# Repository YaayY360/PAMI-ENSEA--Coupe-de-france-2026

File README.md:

# 🔧 Coupe de france de robotique 2026 - PAMI ENSEA 

> **Objectif :** Conception et fabrication d'un robot PAMI (Petit Actionneur Motorisé Indépendant) respectant les modalités attendues pour la coupe de france de robotique 2026.
> 
> **Membres de l'équipe :**
> 
> CHERFI Iftene (1G1)
> 
> EL BAROUD Elias (1G1)
> 
> GRAVE Yanis (1G1)
> 
> LINOT Jean-Bosco (1G1)
> 
> MALEPART Alexandre (1G3)
>
> NEJJARI Mouaad (1G3)
>
> SURESHKUMAR Valentin (1G1)
---

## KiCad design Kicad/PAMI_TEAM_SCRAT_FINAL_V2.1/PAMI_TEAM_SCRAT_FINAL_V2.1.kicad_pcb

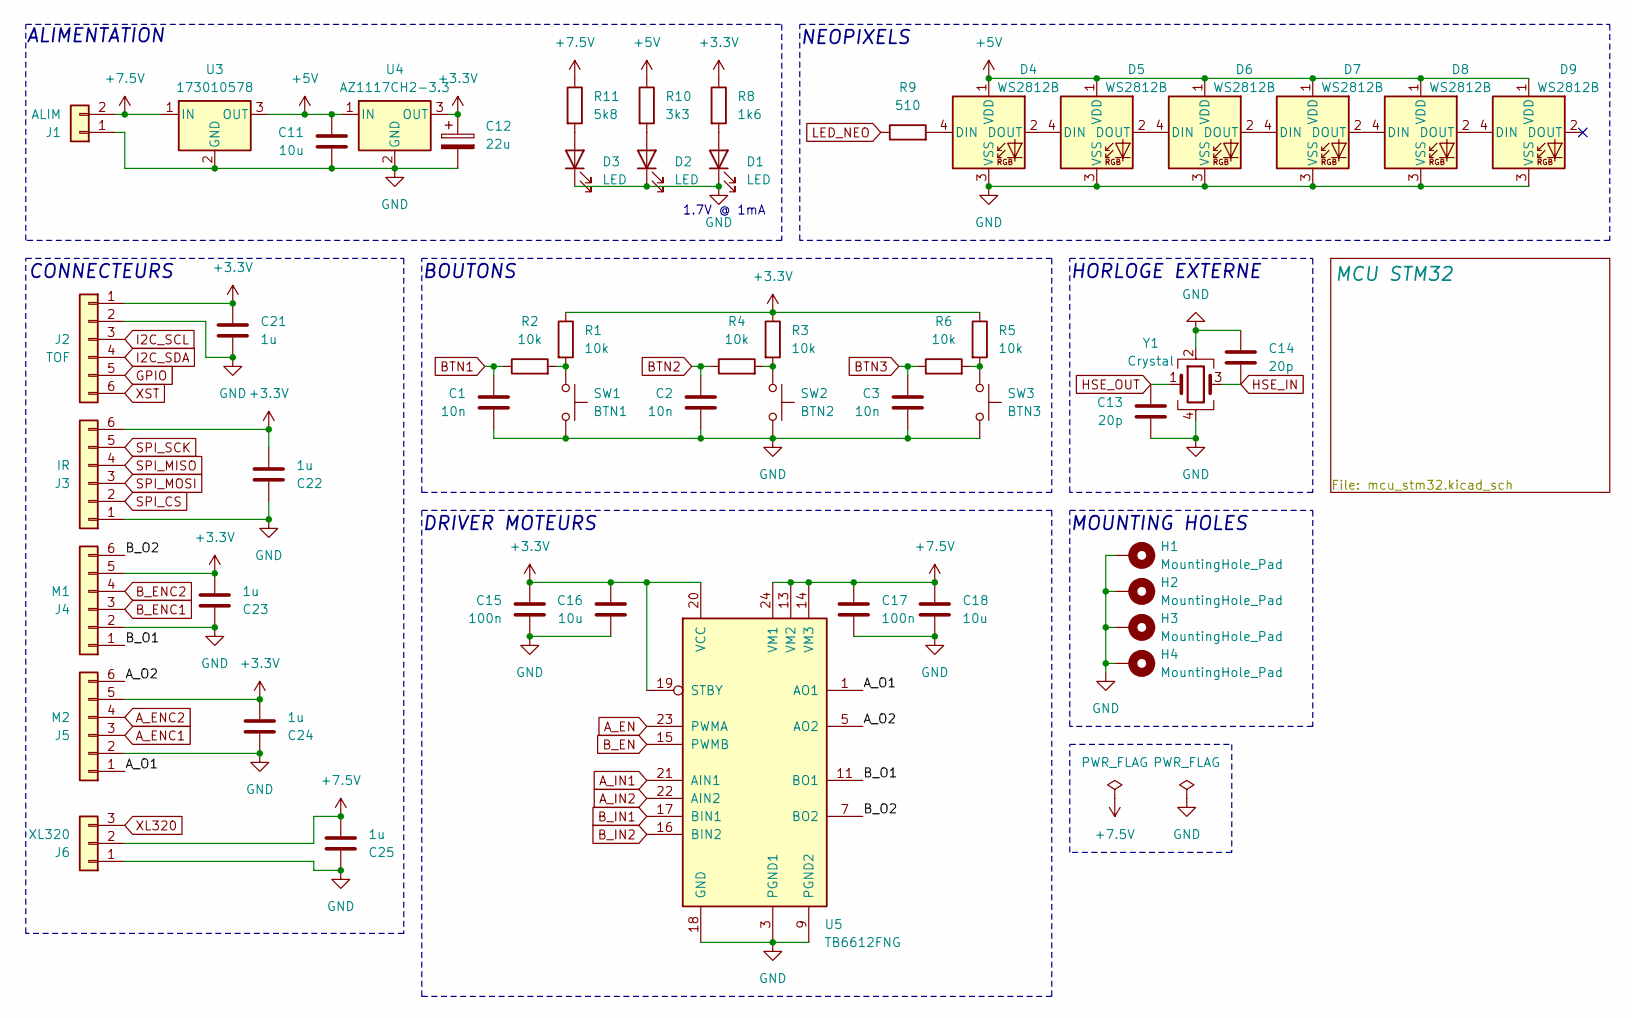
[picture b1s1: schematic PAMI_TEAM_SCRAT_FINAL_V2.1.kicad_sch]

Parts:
C1, C2, C3: 10n; C_0603_1608Metric
C11, C16, C18: 10u; C_0603_1608Metric
C12: 22u; CP_Elec_5x5.4
C13, C14: 20p; C_0603_1608Metric
C15, C17: 100n; C_0603_1608Metric
C21, C22, C23, C24, C25: 1u; C_0603_1608Metric
D1, D2, D3: LED; LED_0603_1608Metric; MPN 150060RS55040
D4, D5, D6, D7, D8, D9: WS2812B; LED_WS2812B_PLCC4_5.0x5.0mm_P3.2mm
H1, H2, H3, H4: MountingHole_Pad; MountingHole_3.2mm_M3_DIN965_Pad
J1: ALIM; JST_XH_B2B-XH-A_1x02_P2.50mm_Vertical
J2: TOF; PinSocket_1x06_P2.54mm_Horizontal
J3: IR; JST_XH_B6B-XH-A_1x06_P2.50mm_Vertical
J4: M1; JST_XH_B6B-XH-A_1x06_P2.50mm_Vertical
J5: M2; JST_XH_B6B-XH-A_1x06_P2.50mm_Vertical
J6: XL320; JST_XH_B3B-XH-A_1x03_P2.50mm_Vertical
R1, R2, R3, R4, R5, R6: 10k; R_0603_1608Metric
R8: 1k6; R_0603_1608Metric
R9: 510; R_0603_1608Metric
R10: 3k3; R_0603_1608Metric
R11: 5k8; R_0603_1608Metric
SW1: BTN1; SW_SPST_PTS645Sx43SMTR92
SW2: BTN2; SW_SPST_PTS645Sx43SMTR92
SW3: BTN3; SW_SPST_PTS645Sx43SMTR92
U3: 173010578; Converter_DCDC_RECOM_R-78E-0.5_THT; MPN 173010578
U4: AZ1117CH2-3.3; SOT-223-3_TabPin2
U5: TB6612FNG; SSOP-24_5.3x8.2mm_P0.65mm
Y1: Crystal; Crystal_SMD_7050-4Pin_7.0x5.0mm

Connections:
+3.3V: C12.1, C15.1, C16.1, C21.1, C22.2, C23.2, C24.2, J2.1, J3.6, J4.5, J5.5, R1.1, R3.1, R5.1, R8.1, U4.3 (OUT), U5.19 (STBY), U5.20 (VCC); also elsewhere on the board
+5V: C11.1, D4.1 (VDD), D5.1 (VDD), D6.1 (VDD), D7.1 (VDD), D8.1 (VDD), D9.1 (VDD), R10.1, U3.3 (OUT), U4.1 (IN)
+7.5V: C17.1, C18.1, C25.2, J1.2, J6.2, R11.1, U3.1 (IN), U5.13 (VM2), U5.14 (VM3), U5.24 (VM1)
/A_O1: J5.1, U5.1 (AO1), U5.2 (AO1)
/A_O2: J5.6, U5.5 (AO2), U5.6 (AO2)
/B_O1: J4.1, U5.11 (BO1), U5.12 (BO1)
/B_O2: J4.6, U5.7 (BO2), U5.8 (BO2)
A_EN: U5.23 (PWMA); also elsewhere on the board
A_ENC1: J5.3; also elsewhere on the board
A_ENC2: J5.4; also elsewhere on the board
A_IN1: U5.21 (AIN1); also elsewhere on the board
A_IN2: U5.22 (AIN2); also elsewhere on the board
BTN1: C1.1, R2.1; also elsewhere on the board
BTN2: C2.1, R4.1; also elsewhere on the board
BTN3: C3.1, R6.1; also elsewhere on the board
B_EN: U5.15 (PWMB); also elsewhere on the board
B_ENC1: J4.3; also elsewhere on the board
B_ENC2: J4.4; also elsewhere on the board
B_IN1: U5.17 (BIN1); also elsewhere on the board
B_IN2: U5.16 (BIN2); also elsewhere on the board
GND: C1.2, C2.2, C3.2, C11.2, C12.2, C13.2, C14.1, C15.2, C16.2, C17.2, C18.2, C21.2, C22.1, C23.1, C24.1, C25.1, D1.1 (K), D2.1 (K), D3.1 (K), D4.3 (VSS), D5.3 (VSS), D6.3 (VSS), D7.3 (VSS), D8.3 (VSS), D9.3 (VSS), H1.1, H2.1, H3.1, H4.1, J1.1, J2.2, J3.1, J4.2, J5.2, J6.1, SW1.2, SW2.2, SW3.2, U3.2 (GND), U4.2 (GND), U5.3 (PGND1), U5.4 (PGND1), U5.9 (PGND2), U5.10 (PGND2), U5.18 (GND), Y1.2, Y1.4; also elsewhere on the board
GPIO: J2.5; also elsewhere on the board
HSE_IN: C14.2, Y1.3; also elsewhere on the board
HSE_OUT: C13.1, Y1.1; also elsewhere on the board
I2C_SCL: J2.3; also elsewhere on the board
I2C_SDA: J2.4; also elsewhere on the board
LED_NEO: R9.1; also elsewhere on the board
unnamed: D1.2 (A), R8.2
unnamed: D2.2 (A), R10.2
unnamed: D3.2 (A), R11.2
unnamed: D4.4 (DIN), R9.2
unnamed: D4.2 (DOUT), D5.4 (DIN)
unnamed: D5.2 (DOUT), D6.4 (DIN)
unnamed: D6.2 (DOUT), D7.4 (DIN)
unnamed: D7.2 (DOUT), D8.4 (DIN)
unnamed: D8.2 (DOUT), D9.4 (DIN)
unnamed: R1.2, R2.2, SW1.1
unnamed: R3.2, R4.2, SW2.1
unnamed: R5.2, R6.2, SW3.1
SPI_CS: J3.2; also elsewhere on the board
SPI_MISO: J3.4; also elsewhere on the board
SPI_MOSI: J3.3; also elsewhere on the board
SPI_SCK: J3.5; also elsewhere on the board
XL320: J6.3; also elsewhere on the board
XST: J2.6; also elsewhere on the board

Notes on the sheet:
CONNECTEURS
MOUNTING HOLES
BOUTONS
NEOPIXELS
HORLOGE EXTERNE
DRIVER MOTEURS
ALIMENTATION
1.7V @ 1mA

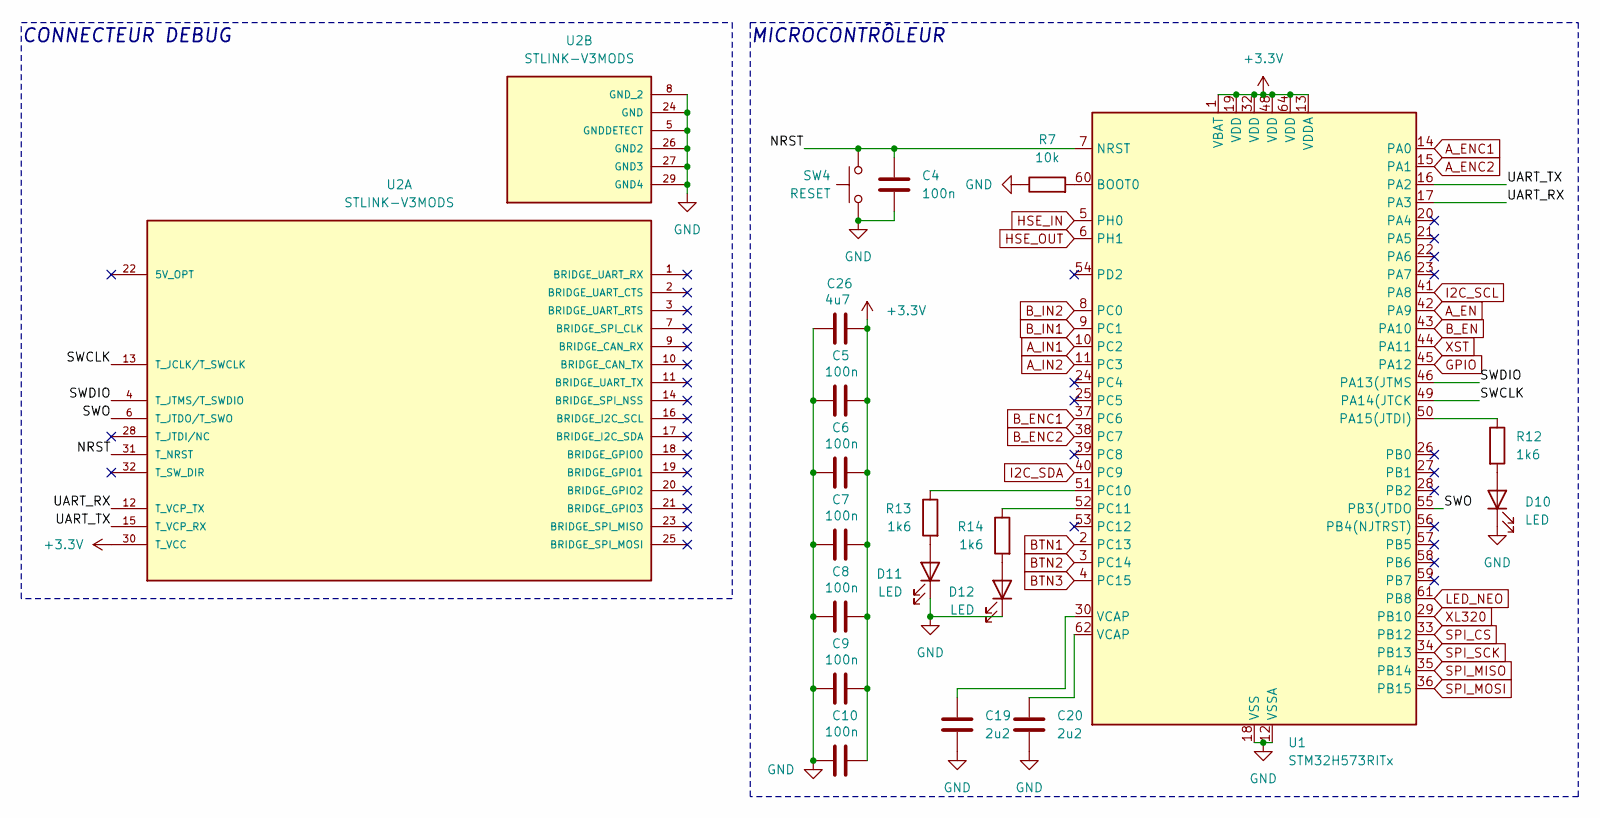
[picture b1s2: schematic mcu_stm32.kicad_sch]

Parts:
C4, C5, C6, C7, C8, C9, C10: 100n; C_0603_1608Metric
C19, C20: 2u2; C_0603_1608Metric
C26: 4u7; C_0603_1608Metric
D10, D11, D12: LED; LED_0603_1608Metric; MPN 150060RS55040
R7: 10k; R_0603_1608Metric
R12, R13, R14: 1k6; R_0603_1608Metric
SW4: RESET; SW_SPST_PTS645Sx43SMTR92
U1: STM32H573RITx; LQFP-64_10x10mm_P0.5mm
U2: STLINK-V3MODS; MODULE_STLINK-V3MODS; PARTREV 1

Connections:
+3.3V: C5.2, C6.2, C7.2, C8.2, C9.2, C10.2, C26.2, U1.1 (VBAT), U1.13 (VDDA), U1.19 (VDD), U1.32 (VDD), U1.48 (VDD), U1.64 (VDD), U2.30 (T_VCC); also elsewhere on the board
/MCU STM32/NRST: C4.1, SW4.1, U1.7 (NRST), U2.31 (T_NRST)
/MCU STM32/SWCLK: U1.49 (PA14(JTCK), U2.13 (T_JCLK/T_SWCLK)
/MCU STM32/SWDIO: U1.46 (PA13(JTMS), U2.4 (T_JTMS/T_SWDIO)
/MCU STM32/SWO: U1.55 (PB3(JTDO), U2.6 (T_JTDO/T_SWO)
/MCU STM32/UART_RX: U1.17 (PA3), U2.12 (T_VCP_TX)
/MCU STM32/UART_TX: U1.16 (PA2), U2.15 (T_VCP_RX)
A_EN: U1.42 (PA9); also elsewhere on the board
A_ENC1: U1.14 (PA0); also elsewhere on the board
A_ENC2: U1.15 (PA1); also elsewhere on the board
A_IN1: U1.10 (PC2); also elsewhere on the board
A_IN2: U1.11 (PC3); also elsewhere on the board
BTN1: U1.2 (PC13); also elsewhere on the board
BTN2: U1.3 (PC14); also elsewhere on the board
BTN3: U1.4 (PC15); also elsewhere on the board
B_EN: U1.43 (PA10); also elsewhere on the board
B_ENC1: U1.37 (PC6); also elsewhere on the board
B_ENC2: U1.38 (PC7); also elsewhere on the board
B_IN1: U1.9 (PC1); also elsewhere on the board
B_IN2: U1.8 (PC0); also elsewhere on the board
GND: C4.2, C5.1, C6.1, C7.1, C8.1, C9.1, C10.1, C19.2, C20.2, C26.1, D10.1 (K), D11.1 (K), D12.1 (K), R7.1, SW4.2, U1.12 (VSSA), U1.18 (VSS), U1.31 (VSS), U1.47 (VSS), U1.63 (VSS), U2.5 (GNDDETECT), U2.8 (GND_2), U2.24 (GND), U2.26 (GND2), U2.27 (GND3), U2.29 (GND4); also elsewhere on the board
GPIO: U1.45 (PA12); also elsewhere on the board
HSE_IN: U1.5 (PH0); also elsewhere on the board
HSE_OUT: U1.6 (PH1); also elsewhere on the board
I2C_SCL: U1.41 (PA8); also elsewhere on the board
I2C_SDA: U1.40 (PC9); also elsewhere on the board
LED_NEO: U1.61 (PB8); also elsewhere on the board
unnamed: C19.1, U1.30 (VCAP)
unnamed: C20.1, U1.62 (VCAP)
unnamed: D10.2 (A), R12.2
unnamed: D11.2 (A), R13.2
unnamed: D12.2 (A), R14.2
unnamed: R7.2, U1.60 (BOOT0)
unnamed: R12.1, U1.50 (PA15(JTDI))
unnamed: R13.1, U1.51 (PC10)
unnamed: R14.1, U1.52 (PC11)
SPI_CS: U1.33 (PB12); also elsewhere on the board
SPI_MISO: U1.35 (PB14); also elsewhere on the board
SPI_MOSI: U1.36 (PB15); also elsewhere on the board
SPI_SCK: U1.34 (PB13); also elsewhere on the board
XL320: U1.29 (PB10); also elsewhere on the board
XST: U1.44 (PA11); also elsewhere on the board

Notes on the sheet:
CONNECTEUR DEBUG
MICROCONTRÔLEUR

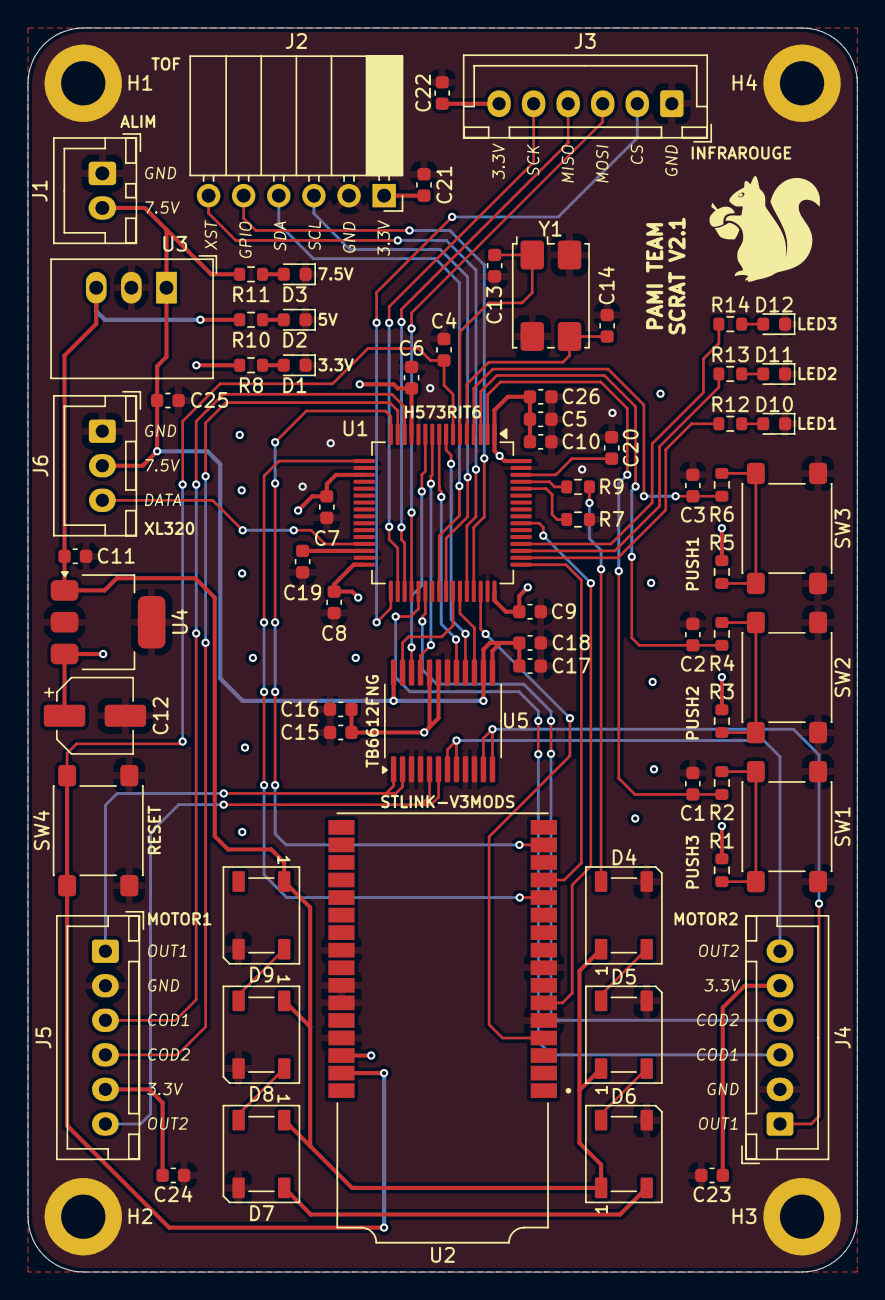
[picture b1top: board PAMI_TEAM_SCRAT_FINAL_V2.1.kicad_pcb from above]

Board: 4 copper layers, 60.0 x 90.0 mm, 72 parts (0 on the bottom side), 60 nets.

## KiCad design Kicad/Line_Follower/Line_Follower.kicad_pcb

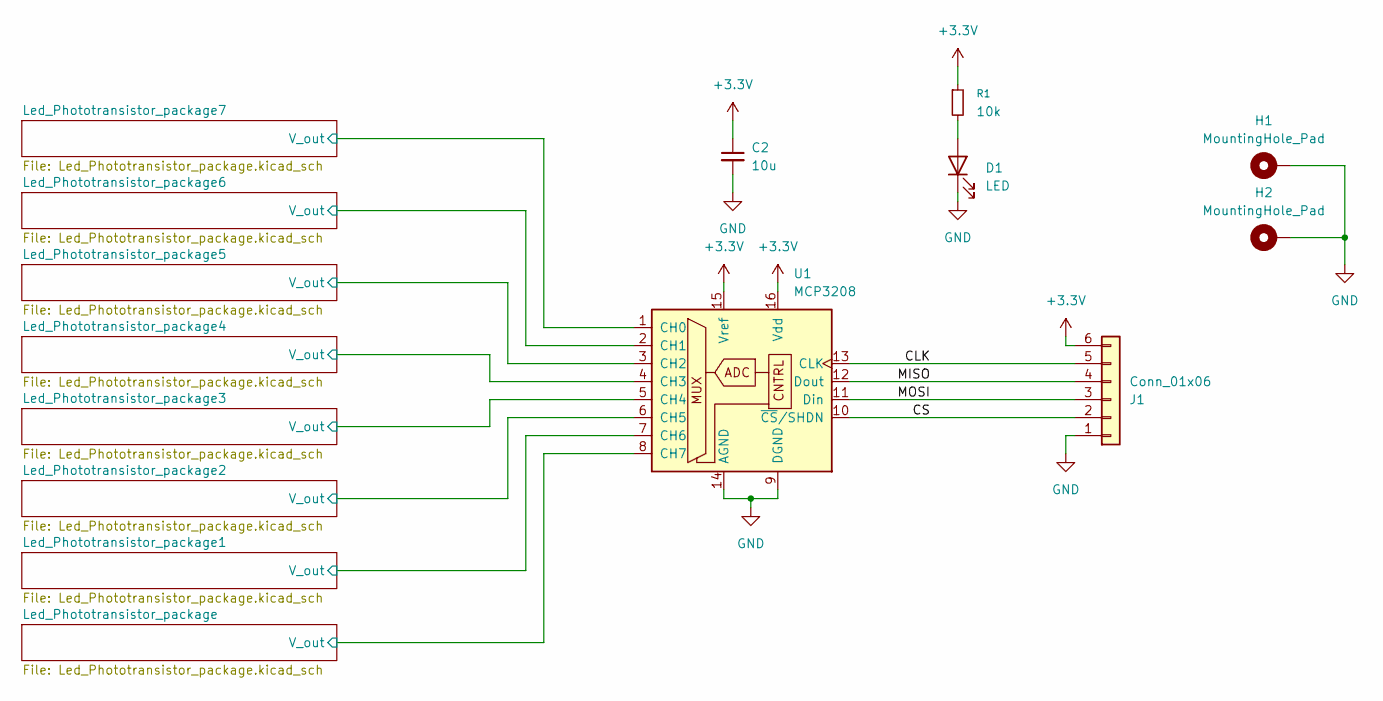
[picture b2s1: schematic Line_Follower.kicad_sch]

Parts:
C2: 10u; C_0603_1608Metric
D1: LED
H1, H2: MountingHole_Pad
J1: Conn_01x06
R1: 10k
U1: MCP3208

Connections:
+3.3V: C2.1, J1.6, R1.1, U1.15 (Vref), U1.16 (Vdd); also elsewhere on the board
/CLK: J1.5, U1.13 (CLK)
/CS: J1.2, U1.10 (~CS/SHDN)
/Led_Phototransistor_package1/V_out: U1.7 (CH6); also elsewhere on the board
/Led_Phototransistor_package2/V_out: U1.6 (CH5); also elsewhere on the board
/Led_Phototransistor_package3/V_out: U1.5 (CH4); also elsewhere on the board
/Led_Phototransistor_package4/V_out: U1.4 (CH3); also elsewhere on the board
/Led_Phototransistor_package5/V_out: U1.3 (CH2); also elsewhere on the board
/Led_Phototransistor_package6/V_out: U1.2 (CH1); also elsewhere on the board
/Led_Phototransistor_package7/V_out: U1.1 (CH0); also elsewhere on the board
/Led_Phototransistor_package/V_out: U1.8 (CH7); also elsewhere on the board
/MISO: J1.4, U1.12 (Dout)
/MOSI: J1.3, U1.11 (Din)
GND: C2.2, D1.1 (K), H1.1, H2.1, J1.1, U1.9 (DGND), U1.14 (AGND); also elsewhere on the board
unnamed: D1.2 (A), R1.2

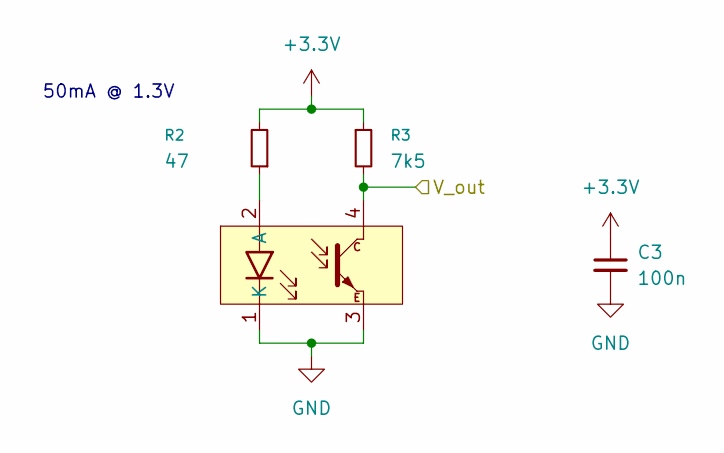
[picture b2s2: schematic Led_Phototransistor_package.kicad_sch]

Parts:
C3: 100n; C_0603_1608Metric
R2: 47
R3: 7k5
U2: (no value)

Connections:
+3.3V: C3.1, R2.2, R3.1; also elsewhere on the board
/Led_Phototransistor_package/V_out: R3.2, U2.4; also elsewhere on the board
GND: C3.2, U2.1 (K), U2.3; also elsewhere on the board
unnamed: R2.1, U2.2 (A)

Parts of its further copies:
C4, C5, C6, C7, C8, C9, C10: 100n; C_0603_1608Metric
R4, R6, R8, R10, R12, R14, R16: 47
R5, R7, R9, R11, R13, R15, R17: 7k5
U3, U4, U5, U6, U7, U8, U9: (no value)

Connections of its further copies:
+3.3V: C4.1, C5.1, C6.1, C7.1, C8.1, C9.1, C10.1, R4.2, R5.1, R6.2, R7.1, R8.2, R9.1, R10.2, R11.1, R12.2, R13.1, R14.2, R15.1, R16.2, R17.1; also elsewhere on the board
/Led_Phototransistor_package1/V_out: R5.2, U3.4; also elsewhere on the board
/Led_Phototransistor_package2/V_out: R7.2, U4.4; also elsewhere on the board
/Led_Phototransistor_package3/V_out: R9.2, U5.4; also elsewhere on the board
/Led_Phototransistor_package4/V_out: R11.2, U6.4; also elsewhere on the board
/Led_Phototransistor_package5/V_out: R13.2, U7.4; also elsewhere on the board
/Led_Phototransistor_package6/V_out: R15.2, U8.4; also elsewhere on the board
/Led_Phototransistor_package7/V_out: R17.2, U9.4; also elsewhere on the board
GND: C4.2, C5.2, C6.2, C7.2, C8.2, C9.2, C10.2, U3.1 (K), U3.3, U4.1 (K), U4.3, U5.1 (K), U5.3, U6.1 (K), U6.3, U7.1 (K), U7.3, U8.1 (K), U8.3, U9.1 (K), U9.3; also elsewhere on the board
unnamed: R4.1, U3.2 (A)
unnamed: R6.1, U4.2 (A)
unnamed: R8.1, U5.2 (A)
unnamed: R10.1, U6.2 (A)
unnamed: R12.1, U7.2 (A)
unnamed: R14.1, U8.2 (A)
unnamed: R16.1, U9.2 (A)

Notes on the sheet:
50mA @ 1.3V

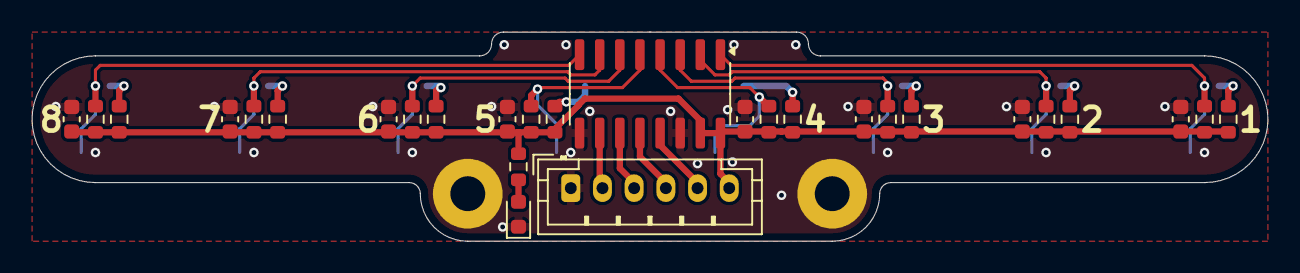
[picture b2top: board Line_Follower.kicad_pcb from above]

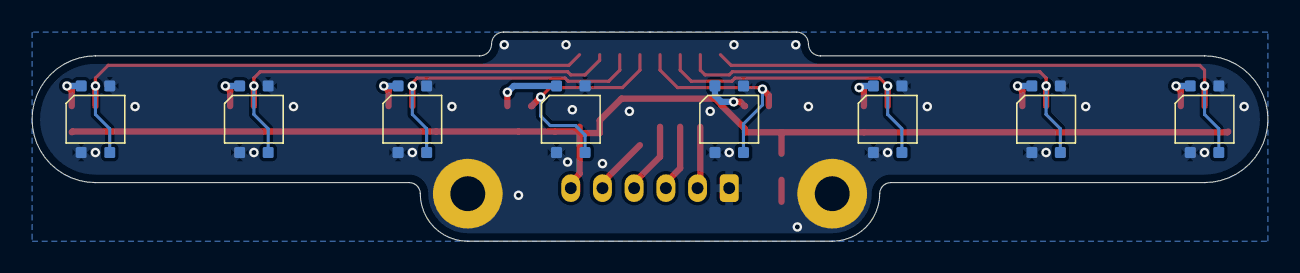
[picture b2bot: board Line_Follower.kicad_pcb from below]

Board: 2 copper layers, 78.0 x 13.2 mm, 38 parts (8 on the bottom side), 23 nets.

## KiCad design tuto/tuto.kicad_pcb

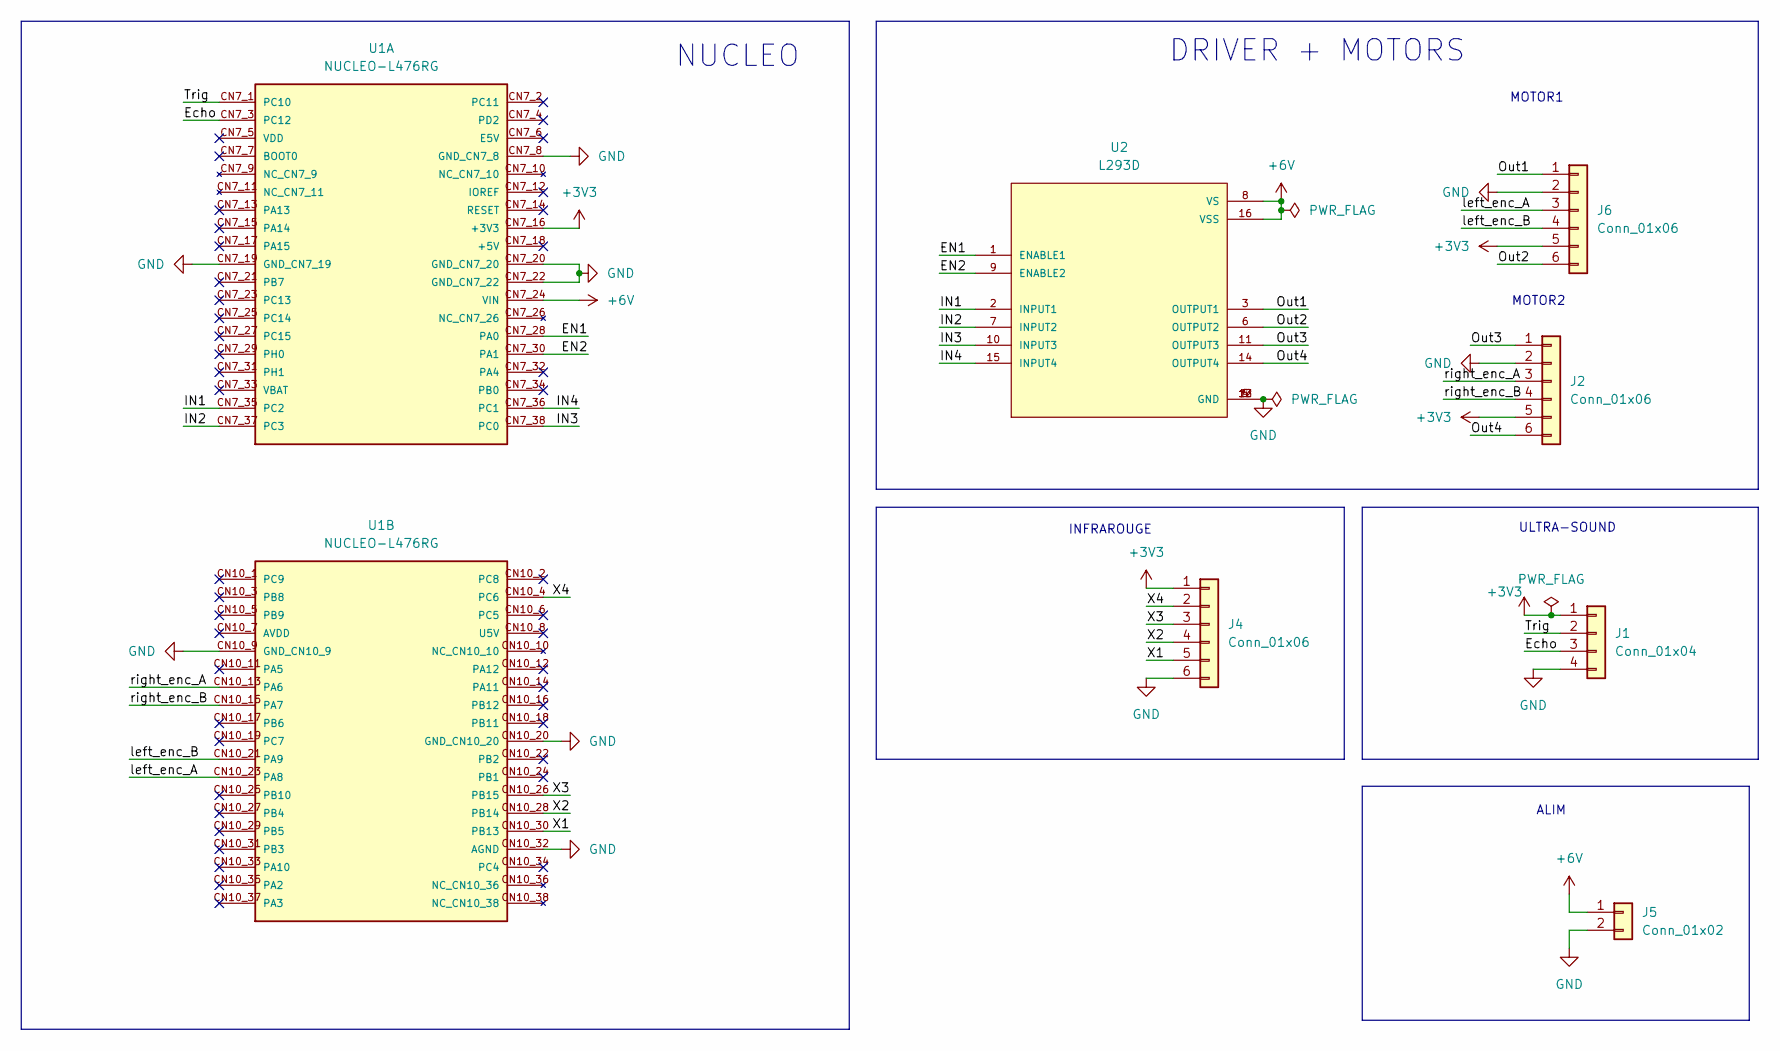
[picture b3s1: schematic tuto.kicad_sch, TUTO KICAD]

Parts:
J1: Conn_01x04; PinHeader_1x04_P2.54mm_Vertical
J2, J4, J6: Conn_01x06; PinHeader_1x06_P2.54mm_Vertical
J5: Conn_01x02; PinHeader_1x02_P2.54mm_Vertical
U1: NUCLEO-L476RG; MODULE_NUCLEO-L476RG; PARTREV 15; DigiKey_Part_Number 497-15881-ND
U2: L293D; DIP880W50P254L2000H510Q16; DigiKey_Part_Number 497-2936-5-ND

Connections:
+3V3: J1.1, J2.5, J4.1, J6.5, U1.CN7_16 (+3V3)
+6V: J5.1, U1.CN7_24 (VIN), U2.8 (VS), U2.16 (VSS)
/EN1: U1.CN7_28 (PA0), U2.1 (ENABLE1)
/EN2: U1.CN7_30 (PA1), U2.9 (ENABLE2)
/Echo: J1.3, U1.CN7_3 (PC12)
/IN1: U1.CN7_35 (PC2), U2.2 (INPUT1)
/IN2: U1.CN7_37 (PC3), U2.7 (INPUT2)
/IN3: U1.CN7_38 (PC0), U2.10 (INPUT3)
/IN4: U1.CN7_36 (PC1), U2.15 (INPUT4)
/Out1: J6.1, U2.3 (OUTPUT1)
/Out2: J6.6, U2.6 (OUTPUT2)
/Out3: J2.1, U2.11 (OUTPUT3)
/Out4: J2.6, U2.14 (OUTPUT4)
/Trig: J1.2, U1.CN7_1 (PC10)
/X1: J4.5, U1.CN10_30 (PB13)
/X2: J4.4, U1.CN10_28 (PB14)
/X3: J4.3, U1.CN10_26 (PB15)
/X4: J4.2, U1.CN10_4 (PC6)
/left_enc_A: J6.3, U1.CN10_23 (PA8)
/left_enc_B: J6.4, U1.CN10_21 (PA9)
/right_enc_A: J2.3, U1.CN10_13 (PA6)
/right_enc_B: J2.4, U1.CN10_15 (PA7)
GND: J1.4, J2.2, J4.6, J5.2, J6.2, U1.CN7_8 (GND_CN7_8), U1.CN7_19 (GND_CN7_19), U1.CN7_20 (GND_CN7_20), U1.CN7_22 (GND_CN7_22), U1.CN10_9 (GND_CN10_9), U1.CN10_20 (GND_CN10_20), U1.CN10_32 (AGND), U2.4 (GND), U2.5 (GND), U2.12 (GND), U2.13 (GND)

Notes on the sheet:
MOTOR1
MOTOR2
DRIVER + MOTORS
NUCLEO
ALIM
INFRAROUGE
ULTRA-SOUND

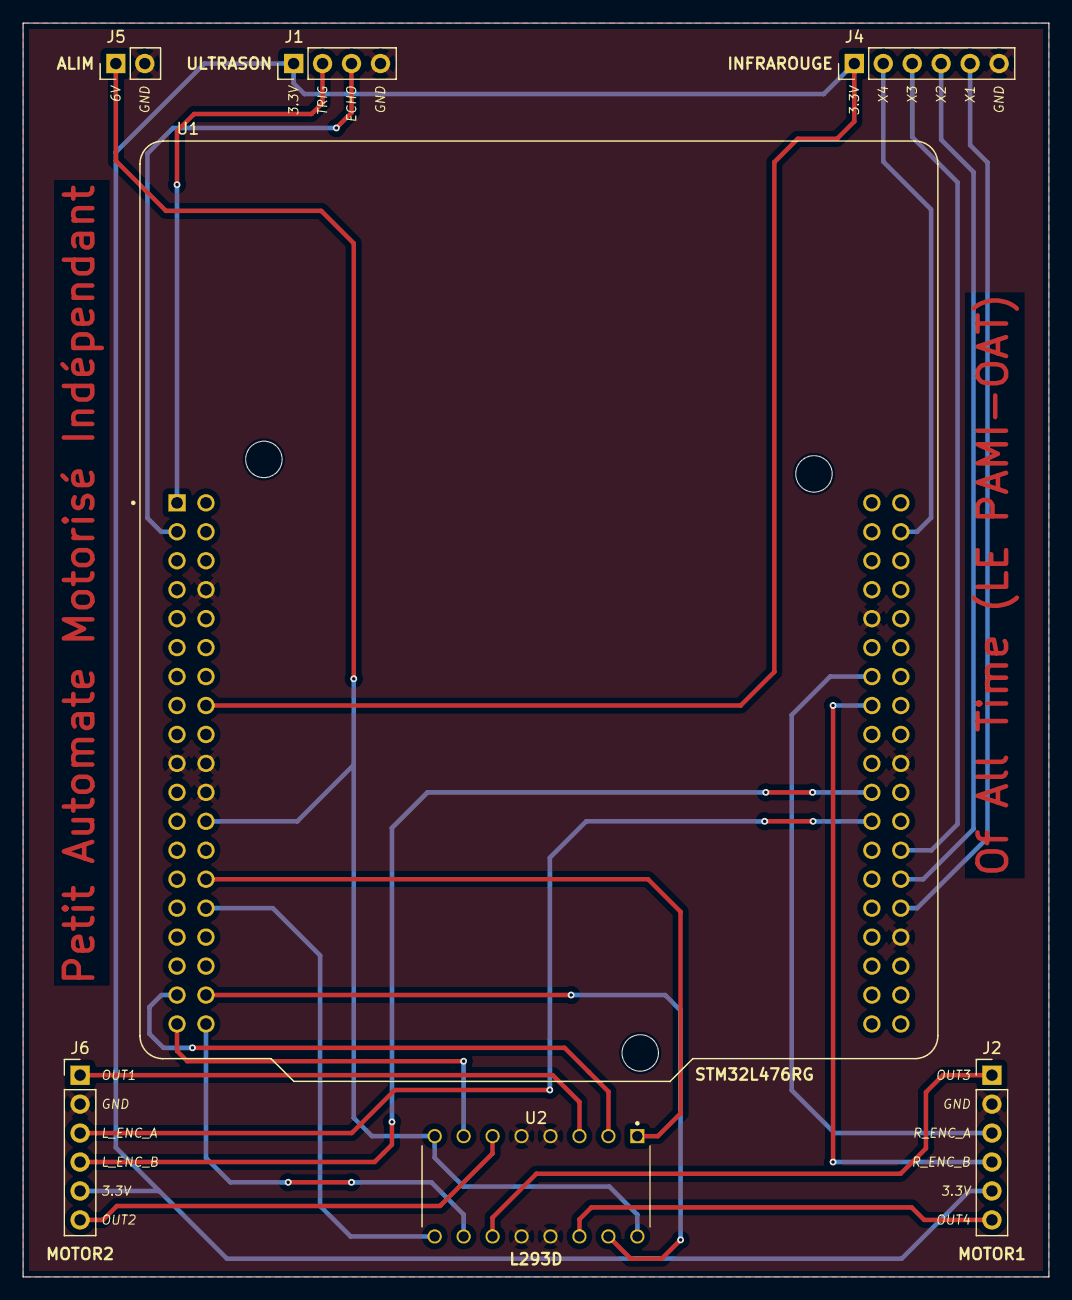
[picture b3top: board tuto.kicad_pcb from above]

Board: 2 copper layers, 90.0 x 110.0 mm, 7 parts (0 on the bottom side), 23 nets.

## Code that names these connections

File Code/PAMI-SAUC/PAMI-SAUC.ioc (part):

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Mcu.Name=STM32H573RITx
Mcu.Package=LQFP64
Mcu.UserName=STM32H573RITx
PA0.Signal=S_TIM2_CH1
PA1.Signal=S_TIM2_CH2
PA10.Signal=S_TIM1_CH3
PA11.GPIOParameters=GPIO_Label
PA11.GPIO_Label=XST
PA11.Signal=GPIO_Output
PA12.GPIOParameters=GPIO_Label
PA12.GPIO_Label=GPIO1
PA12.Signal=GPIO_Input
PA13(JTMS/SWDIO).Mode=Trace_Asynchronous_SW
PA13(JTMS/SWDIO).Signal=DEBUG_JTMS-SWDIO
PA14(JTCK/SWCLK).Mode=Trace_Asynchronous_SW
PA14(JTCK/SWCLK).Signal=DEBUG_JTCK-SWCLK
PA15(JTDI).GPIOParameters=GPIO_Label
PA15(JTDI).GPIO_Label=LED1
PA15(JTDI).Signal=GPIO_Output
PA2.Mode=Asynchronous
PA2.Signal=USART2_TX
PA3.Mode=Asynchronous
PA3.Signal=USART2_RX
PA8.Mode=I2C
PA8.Signal=I2C3_SCL
PA9.Signal=S_TIM1_CH2
PB12.GPIOParameters=GPIO_Label
PB12.GPIO_Label=SPI2_CS
PB12.Signal=GPIO_Output
PB13.Mode=Full_Duplex_Master
PB13.Signal=SPI2_SCK
PB14.Mode=Full_Duplex_Master
PB14.Signal=SPI2_MISO
PB15.Mode=Full_Duplex_Master
PB15.Signal=SPI2_MOSI
PB3(JTDO/TRACESWO).Mode=Trace_Asynchronous_SW
PB3(JTDO/TRACESWO).Signal=DEBUG_JTDO-SWO
PB8.Signal=S_TIM4_CH3
PC0.GPIOParameters=GPIO_Label
PC0.GPIO_Label=B_IN2
PC0.Signal=GPIO_Output
PC1.GPIOParameters=GPIO_Label
PC1.GPIO_Label=B_IN1
PC1.Signal=GPIO_Output
PC10.GPIOParameters=GPIO_Label
PC10.GPIO_Label=LED2
PC10.Signal=GPIO_Output
PC11.GPIOParameters=GPIO_Label
PC11.GPIO_Label=LED3
PC11.Signal=GPIO_Output
PC13.GPIOParameters=GPIO_PuPd,GPIO_Label
PC13.GPIO_Label=BTN1
PC13.GPIO_PuPd=GPIO_PULLUP
PC13.Signal=GPXTI13
PC14-OSC32_IN(OSC32_IN).GPIOParameters=GPIO_PuPd,GPIO_Label
PC14-OSC32_IN(OSC32_IN).GPIO_Label=BTN2
PC14-OSC32_IN(OSC32_IN).GPIO_PuPd=GPIO_PULLUP
PC14-OSC32_IN(OSC32_IN).Signal=GPXTI14
PC15-OSC32_OUT(OSC32_OUT).GPIOParameters=GPIO_PuPd,GPIO_Label
PC15-OSC32_OUT(OSC32_OUT).GPIO_Label=BTN3
PC15-OSC32_OUT(OSC32_OUT).GPIO_PuPd=GPIO_PULLUP
PC15-OSC32_OUT(OSC32_OUT).Signal=GPXTI15
PC2.GPIOParameters=GPIO_Label
PC2.GPIO_Label=A_IN1
PC2.Signal=GPIO_Output
PC3.GPIOParameters=GPIO_Label
PC3.GPIO_Label=A_IN2
PC3.Signal=GPIO_Output
PC6.Signal=S_TIM3_CH1
PC7.Signal=S_TIM3_CH2
PC8.Signal=S_TIM8_CH3
PC9.Mode=I2C
PC9.Signal=I2C3_SDA
PH0-OSC_IN(PH0).Mode=HSE-External-Oscillator
PH0-OSC_IN(PH0).Signal=RCC_OSC_IN
PH1-OSC_OUT(PH1).Mode=HSE-External-Oscillator
PH1-OSC_OUT(PH1).Signal=RCC_OSC_OUT
RCC.HSE_VALUE=25000000
RCC.SYSCLKFreq_VALUE=32000000
board=custom

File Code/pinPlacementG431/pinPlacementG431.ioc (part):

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Mcu.Name=STM32G431K(6-8-B)Tx
Mcu.Package=LQFP32
Mcu.UserName=STM32G431KBTx
PA0.GPIOParameters=GPIO_Label
PA0.GPIO_Label=ENC_1_A
PA0.Signal=S_TIM2_CH1
PA1.Signal=S_TIM2_CH2
PA10.GPIOParameters=GPIO_Label
PA10.GPIO_Label=BTN_1
PA10.Signal=GPXTI10
PA11.Signal=S_TIM4_CH1
PA12.Signal=S_TIM4_CH2
PA13.Mode=Trace_Asynchronous_SW
PA13.Signal=SYS_JTMS-SWDIO
PA14.Mode=Trace_Asynchronous_SW
PA14.Signal=SYS_JTCK-SWCLK
PA15.GPIOParameters=GPIO_Label
PA15.GPIO_Label=SPI_CS
PA15.Signal=GPIO_Output
PA2.Mode=Asynchronous
PA2.Signal=USART2_TX
PA3.Mode=Asynchronous
PA3.Signal=USART2_RX
PA4.Signal=S_TIM3_CH2
PA5.Mode=Full_Duplex_Master
PA5.Signal=SPI1_SCK
PA6.Signal=S_TIM3_CH1
PA7.GPIOParameters=GPIO_Label
PA7.GPIO_Label=BTN_3
PA7.Signal=GPXTI7
PA8.Mode=I2C
PA8.Signal=I2C2_SDA
PA9.Mode=I2C
PA9.Signal=I2C2_SCL
PB0.GPIOParameters=GPIO_Label
PB0.GPIO_Label=BTN_2
PB0.Signal=GPXTI0
PB3.Mode=Trace_Asynchronous_SW
PB3.Signal=SYS_JTDO-SWO
PB4.Mode=Full_Duplex_Master
PB4.Signal=SPI1_MISO
PB5.Mode=Full_Duplex_Master
PB5.Signal=SPI1_MOSI
PB6.Mode=Asynchronous
PB6.Signal=USART1_TX
PB7.Mode=Asynchronous
PB7.Signal=USART1_RX
PB8-BOOT0.Signal=S_TIM16_CH1
PF0-OSC_IN.Mode=HSE-External-Oscillator
PF0-OSC_IN.Signal=RCC_OSC_IN
PF1-OSC_OUT.Mode=HSE-External-Oscillator
PF1-OSC_OUT.Signal=RCC_OSC_OUT
RCC.HSE_VALUE=24000000
RCC.SYSCLKFreq_VALUE=170000000
RCC.SYSCLKSource=RCC_SYSCLKSOURCE_PLLCLK
board=custom

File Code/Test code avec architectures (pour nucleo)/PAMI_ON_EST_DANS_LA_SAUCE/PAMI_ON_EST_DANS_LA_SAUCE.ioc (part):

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Mcu.Name=STM32F303K(6-8)Tx
Mcu.Package=LQFP32
Mcu.UserName=STM32F303K8Tx
PA0.Signal=S_TIM2_CH1_ETR
PA1.Signal=S_TIM2_CH2
PA10.GPIOParameters=GPIO_Label,GPIO_ModeDefaultEXTI
PA10.GPIO_Label=ECHO
PA10.GPIO_ModeDefaultEXTI=GPIO_MODE_IT_RISING_FALLING
PA10.Signal=GPXTI10
PA11.Signal=S_TIM1_CH4
PA13.GPIOParameters=GPIO_Label
PA13.GPIO_Label=SWDIO
PA13.Mode=Serial_Wire
PA13.Signal=SYS_JTMS-SWDIO
PA14.GPIOParameters=GPIO_Label
PA14.GPIO_Label=SWCLK
PA14.Mode=Serial_Wire
PA14.Signal=SYS_JTCK-SWCLK
PA15.Mode=Asynchronous
PA15.Signal=USART2_RX
PA2.Mode=Asynchronous
PA2.Signal=USART2_TX
PA3.GPIOParameters=GPIO_Label
PA3.GPIO_Label=IN2
PA3.Signal=GPIO_Output
PA4.Signal=S_TIM3_CH2
PA5.GPIOParameters=GPIO_Label
PA5.GPIO_Label=IN4
PA5.Signal=GPIO_Output
PA6.Signal=S_TIM3_CH1
PA7.GPIOParameters=GPIO_Label
PA7.GPIO_Label=IN3
PA7.Signal=GPIO_Output
PA8.Signal=S_TIM1_CH1
PA9.GPIOParameters=GPIO_Label
PA9.GPIO_Label=TRIG
PA9.Signal=GPIO_Output
PB0.GPIOParameters=GPIO_Label
PB0.GPIO_Label=X1
PB0.Signal=GPIO_Input
PB1.GPIOParameters=GPIO_Label
PB1.GPIO_Label=X4
PB1.Signal=GPIO_Input
PB3.GPIOParameters=GPIO_Label
PB3.GPIO_Label=IN1
PB3.Signal=GPIO_Output
PB6.GPIOParameters=GPIO_Label
PB6.GPIO_Label=X3
PB6.Signal=GPIO_Input
PB7.GPIOParameters=GPIO_Label
PB7.GPIO_Label=X2
PB7.Signal=GPIO_Input
PF0\ /\ OSC_IN.GPIOParameters=GPIO_Label
PF0\ /\ OSC_IN.GPIO_Label=MCO
PF0\ /\ OSC_IN.Mode=HSE-External-Clock-Source
PF0\ /\ OSC_IN.Signal=RCC_OSC_IN
RCC.HSEPLLFreq_Value=8000000
RCC.HSE_VALUE=8000000
RCC.SYSCLKFreq_VALUE=72000000
RCC.SYSCLKSourceVirtual=RCC_SYSCLKSOURCE_PLLCLK
board=NUCLEO-F303K8
boardIOC=true

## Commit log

2025-10-18 Update project name for 2026
2025-10-18 Revise README with new title and team members
    Updated project title and added team member details.
2025-10-18 Fix formatting issues in README.md
2025-10-18 Format team members list in README.md
2025-10-18 Fix spelling error in README objective
    Corrected the spelling of 'modalité' to 'modalités'.
2025-10-23 Add contributor iftene CHERFI to README
2025-10-23 Fix formatting in README header
2025-10-23 Correct spelling and add new contributors
2025-10-23 Correct spelling of 'Garcia' in README
2025-10-23 Add tasks section to README
    Added a tasks section with assigned responsibilities.
2025-10-23 Add tasks for various components in README
2025-10-23 Update line follower sensor contributors in README
2025-10-26 Add files via upload
    Première version du résumé du règlement de la compétition pour notre PAMI.
2025-11-03 Add ultrasonic distance measurement with HC-SR04
    This file implements an ultrasonic distance measurement using the HC-SR04 sensor. It includes initialization of peripherals, GPIO, and UART for output.
2025-11-13 Add light sensor reading and status reporting
    Implement light sensor functionality to read sensor states and print system status.
2025-11-13 Rename Script_sensor_HC-SR04 to capteurs/Script_sensor_HC-SR04
2025-11-13 Add light_sensor.h header file with setup and loop functions
2025-12-11 Revise team member information in README
    Updated team member details with additional information.
2025-12-11 test
2025-12-11 delete
2025-12-11 ajout_du_code
2026-01-12 ajout des fichier kicad
2026-01-12 ajout datasheet pin
2026-02-02 testjean
2026-02-02 suppression
2026-02-02 restructuration des fichiers
2026-02-02 ajout du premier fichier 3D
2026-02-02 ajout du répertoire pour les datasheets
2026-02-02 ajout XL-320-dimension
2026-02-02 Test Elias github
2026-02-02 Suppression test Elias
2026-02-02 test alex
2026-02-02 G431KBT6 pin placement
2026-02-03 ajout datasheet
2026-02-03 ajout de la liste des composant
2026-02-05 test push valentin
2026-02-05 suppresion du fichier valentin
2026-02-05 renseignement des composant et leu référence
2026-02-05 fusion
2026-02-09 prog du tof
2026-02-09 suppression fichier inutile
2026-02-09 ajout prog tof
2026-02-09 update prog TOF
2026-02-09 ajout de la datasheet du régu 5V
2026-02-09 kicad
2026-02-16 update pcb
2026-02-16 code H573
2026-02-16 prog IR
2026-02-16 3eme commit
2026-02-16 code tof F411RE
2026-02-16 Code H5
2026-02-16 PamiH573
2026-02-16 diagramme architecture
2026-02-16 architecture
2026-02-19 pcb termine
2026-03-09 actualisation liste composants
2026-03-09 copy line follower project
2026-04-05 correctif projet lisibilité
2026-04-05 ajout dernière version du code
2026-04-07 ajout du fichier rassemblant le code
2026-04-09 ajout du code pour architecture software
2026-04-13 ajout fichier architecture code
2026-04-13 ajout diagramme etat
2026-04-17 Nouvelle version de la carte avec les corrections
2026-04-17 nouveau fichier gerber
2026-04-23 ajout code stlink fonctionnel
2026-05-06 Correction de la liaison UART avec le STLINK
